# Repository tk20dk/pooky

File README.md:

# pooky
I2S Amplifier for Krieger/Andy prototype board

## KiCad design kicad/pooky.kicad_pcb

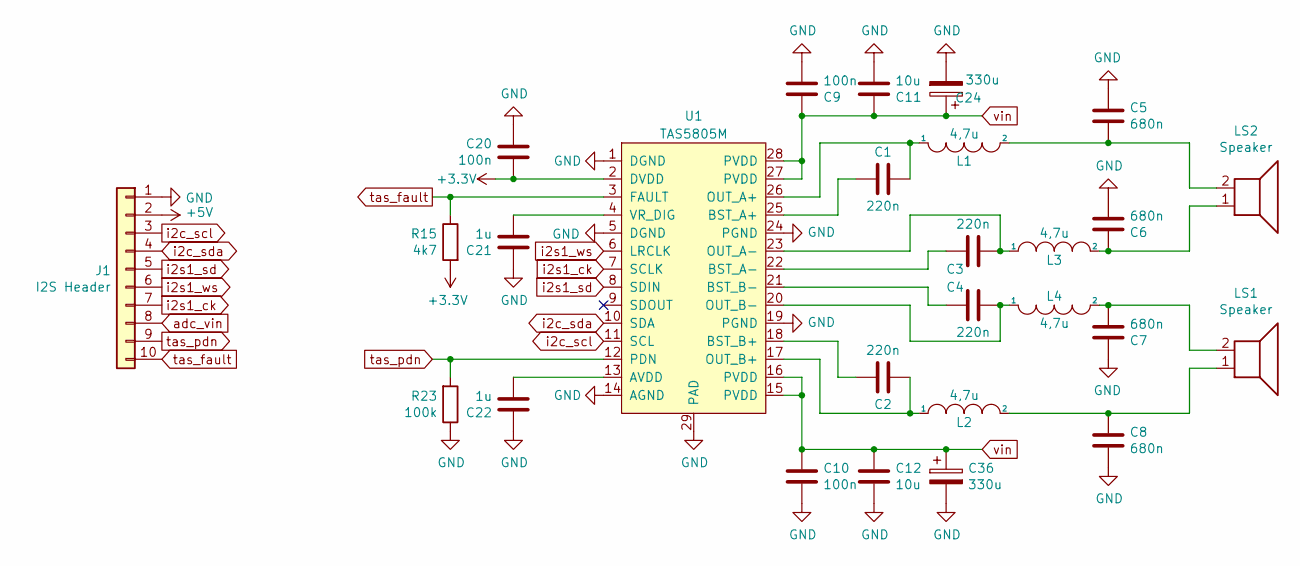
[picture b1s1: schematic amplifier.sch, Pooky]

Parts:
C1, C2, C3, C4: 220n; C_0603_1608Metric
C5, C6, C7, C8: 680n; C_0805_2012Metric
C9, C10, C20: 100n; C_0603_1608Metric
C11, C12: 10u; C_0805_2012Metric
C21, C22: 1u; C_0603_1608Metric
C24, C36: 330u; CP_Elec_8x11.9
J1: I2S Header; PinHeader_1x10_P2.54mm_Horizontal
L1, L2, L3, L4: 4,7u; L_6.3x6.3_H3
LS1, LS2: Speaker; TerminalBlock_RND_205-00001_1x02_P5.00mm_Horizontal
R15: 4k7; R_0603_1608Metric
R23: 100k; R_0603_1608Metric
U1: TAS5805M; HTSSOP-28-1EP_4.4x9.7mm_P0.65mm_EP3.4x9.5mm_Mask2.4x6.17mm_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

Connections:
+3V3: C20.2, R15.2, U1.2 (DVDD); also elsewhere on the board
+5V: J1.2; also elsewhere on the board
GND: C5.1, C6.2, C7.1, C8.2, C9.2, C10.2, C11.2, C12.2, C20.1, C21.1, C22.1, C24.2, C36.2, J1.1, R23.1, U1.1 (DGND), U1.5 (DGND), U1.14 (AGND), U1.19 (PGND), U1.24 (PGND), U1.29 (PAD); also elsewhere on the board
unnamed: C1.1, U1.25 (BST_A+)
unnamed: C1.2, L1.1, U1.26 (OUT_A+)
unnamed: C2.1, U1.18 (BST_B+)
unnamed: C2.2, L2.1, U1.17 (OUT_B+)
unnamed: C3.1, U1.22 (BST_A-)
unnamed: C3.2, L3.1, U1.23 (OUT_A-)
unnamed: C4.1, U1.21 (BST_B-)
unnamed: C4.2, L4.1, U1.20 (OUT_B-)
unnamed: C5.2, L1.2, LS2.2
unnamed: C6.1, L3.2, LS2.1
unnamed: C7.2, L4.2, LS1.2
unnamed: C8.1, L2.2, LS1.1
unnamed: C21.2, U1.4 (VR_DIG)
unnamed: C22.2, U1.13 (AVDD)
adc_vin: J1.8; also elsewhere on the board
i2c_scl: J1.3, U1.11 (SCL)
i2c_sda: J1.4, U1.10 (SDA)
i2s1_ck: J1.7, U1.7 (SCLK)
i2s1_sd: J1.5, U1.8 (SDIN)
i2s1_ws: J1.6, U1.6 (LRCLK)
tas_fault: J1.10, R15.1, U1.3 (FAULT)
tas_pdn: J1.9, R23.2, U1.12 (PDN)
vin: C9.1, C10.1, C11.1, C12.1, C24.1, C36.1, U1.15 (PVDD), U1.16 (PVDD), U1.27 (PVDD), U1.28 (PVDD); also elsewhere on the board

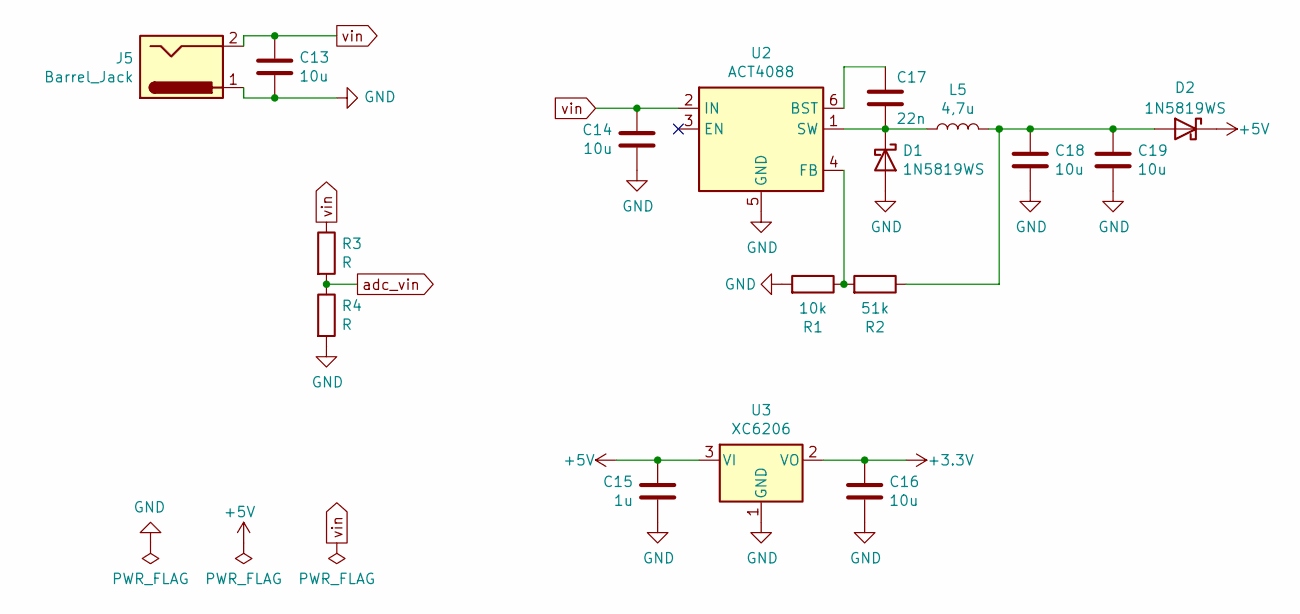
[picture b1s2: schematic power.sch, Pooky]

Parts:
C13, C14, C16, C18, C19: 10u; C_0805_2012Metric
C15: 1u; C_0805_2012Metric
C17: 22n; C_0603_1608Metric
D1, D2: 1N5819WS; D_SOD-323
J5: Barrel_Jack; BarrelJack_Horizontal
L5: 4,7u; L_Coilcraft_XxL4040
R1: 10k; R_0603_1608Metric
R2: 51k; R_0603_1608Metric
R3, R4: R; R_0603_1608Metric
U2: ACT4088; SOT-23-6
U3: XC6206; SOT-23

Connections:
+3V3: C16.1, U3.2 (VO); also elsewhere on the board
+5V: C15.1, D2.1 (K), U3.3 (VI); also elsewhere on the board
GND: C13.2, C14.2, C15.2, C16.2, C18.2, C19.2, D1.2 (A), J5.1, R1.2, R4.2, U2.5 (GND), U3.1 (GND); also elsewhere on the board
unnamed: C17.1, U2.6 (BST)
unnamed: C17.2, D1.1 (K), L5.1, U2.1 (SW)
unnamed: C18.1, C19.1, D2.2 (A), L5.2, R2.1
unnamed: R1.1, R2.2, U2.4 (FB)
adc_vin: R3.2, R4.1; also elsewhere on the board
vin: C13.1, C14.1, J5.2, R3.1, U2.2 (IN); also elsewhere on the board

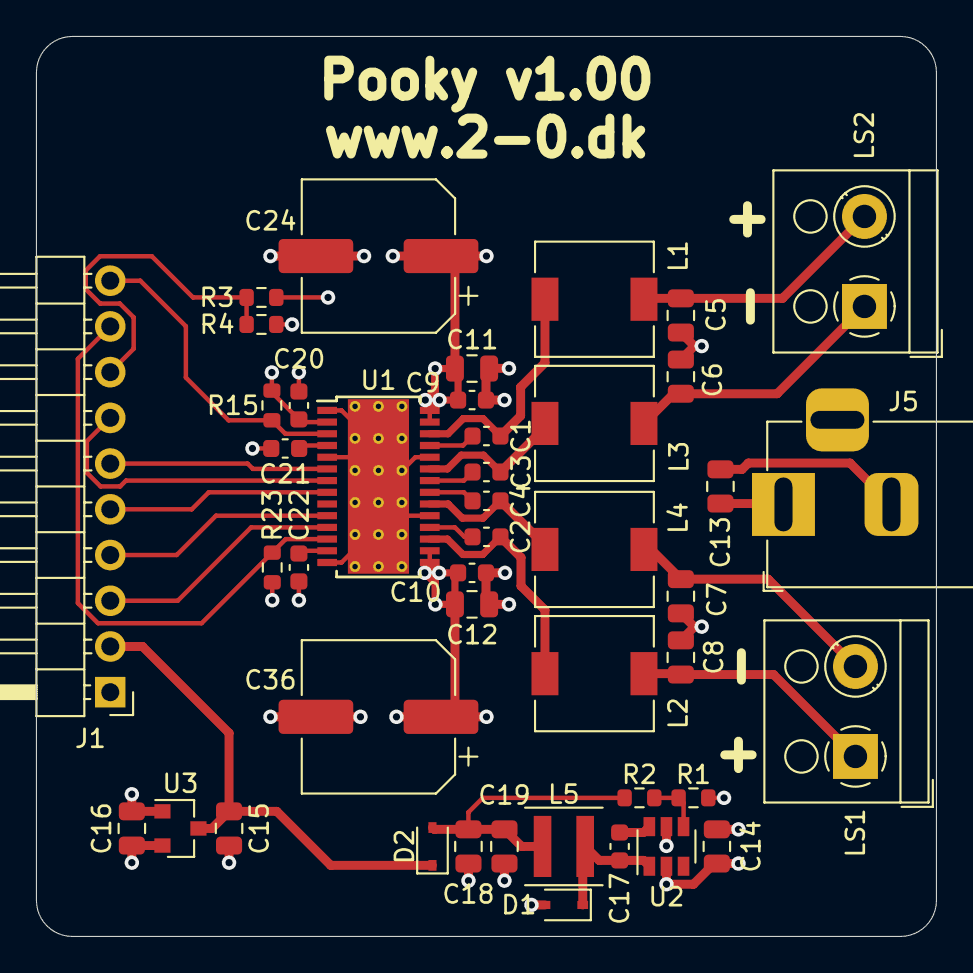
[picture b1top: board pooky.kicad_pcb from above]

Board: 4 copper layers, 50.0 x 50.0 mm, 44 parts (0 on the bottom side), 30 nets.

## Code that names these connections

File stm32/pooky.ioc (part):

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Mcu.Name=STM32F446R(C-E)Tx
Mcu.Package=LQFP64
Mcu.UserName=STM32F446RETx
PA11.Mode=Device_Only
PA11.Signal=USB_OTG_FS_DM
PA12.Mode=Device_Only
PA12.Signal=USB_OTG_FS_DP
PA13.Mode=Serial_Wire
PA13.Signal=SYS_JTMS-SWDIO
PA14.Mode=Serial_Wire
PA14.Signal=SYS_JTCK-SWCLK
PA15.Mode=CEC_Activate
PA15.Signal=CEC
PA3.Mode=SAI_A_AsyncSlave
PA3.Signal=SAI1_FS_A
PA4.Mode=Half_Duplex_Master
PA4.Signal=I2S1_WS
PA5.Mode=Half_Duplex_Master
PA5.Signal=I2S1_CK
PA6.Mode=Master_Clock_Activated
PA6.Signal=I2S2_MCK
PA7.Mode=Half_Duplex_Master
PA7.Signal=I2S1_SD
PA8.Mode=Clock-out-1
PA8.Signal=RCC_MCO_1
PA9.Mode=SAI_B_MasterWithClock
PA9.Signal=SAI1_SD_B
PB10.Mode=SAI_A_AsyncSlave
PB10.Signal=SAI1_SCK_A
PB12.Mode=SAI_B_MasterWithClock
PB12.Signal=SAI1_SCK_B
PB13.Mode=Half_Duplex_Master
PB13.Signal=I2S2_CK
PB4.Mode=Half_Duplex_Master
PB4.Signal=I2S2_WS
PB6.Mode=I2C
PB6.Signal=I2C1_SCL
PB7.Mode=I2C
PB7.Signal=I2C1_SDA
PB9.Mode=SAI_B_MasterWithClock
PB9.Signal=SAI1_FS_B
PC0.Mode=SAI_B_MasterWithClock
PC0.Signal=SAI1_MCLK_B
PC1.Mode=SAI_A_AsyncSlave
PC1.Signal=SAI1_SD_A
PC10.Mode=Asynchronous
PC10.Signal=USART3_TX
PC11.Mode=Asynchronous
PC11.Signal=USART3_RX
PC3.Mode=Half_Duplex_Master
PC3.Signal=I2S2_SD
PC4.Mode=IN2
PC4.Signal=SPDIFRX_IN2
PC5.Mode=IN3
PC5.Signal=SPDIFRX_IN3
PC7.Mode=IN1
PC7.Signal=SPDIFRX_IN1
PC9.Mode=Audio_ClockIn
PC9.Signal=I2S_CKIN
PH0-OSC_IN.Mode=HSE-External-Oscillator
PH0-OSC_IN.Signal=RCC_OSC_IN
PH1-OSC_OUT.Mode=HSE-External-Oscillator
PH1-OSC_OUT.Signal=RCC_OSC_OUT
RCC.HSE_VALUE=8000000
RCC.SYSCLKFreq_VALUE=50000000
RCC.SYSCLKSource=RCC_SYSCLKSOURCE_PLLCLK
board=custom

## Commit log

2021-06-05 Pooky v1.00
